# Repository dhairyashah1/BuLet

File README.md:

# BuLET: An Ultra Low Energy Transmitter

This repository contains the code and artifacts for **BuLet** which is developed as a part of CS5272: Embedded Software Design Course Project, Spring 2025 held at NUS.

> The BuLET system aims to enable low-power BLE
advertisement transmissions in the 1M / 2M PHY modes with
the provision of Extended PHY later. These transmissions are
decodable by commodity BLE receivers like smartphones:

<div align="center">

</div>

## Abstract

Increased embedded system deployments have driven the widespread adoption of various wireless standards. Commonly used protocols include Wi-Fi, Bluetooth, ZigBee, and LoRa operate in the Industrial, Scientific and Medical bands (ISM) i.e. 868 MHz and 2.4 GHz showing their ubiquity and allowance for unlicensed transmissions. Despite advancements in low-power sensors and microcontrollers, the wireless radio subsystem—particularly its analog front end—remains a major power bottleneck in embedded IoT devices. Classic Bluetooth and Bluetooth Low Energy (BLE) dominate short-range wireless communication in the 2.4 GHz spectrum, with BLE favored for its energy efficiency in lightweight, battery-powered applications. However, even state-of-the-art BLE transmitters typically consume around 20 mW  to hundreds to milliwatts, limiting lifetime for battery-operated devices. Existing low-power solutions, such as BLE backscatter, decrease transmission power but rely on external emitters to generate carrier signals, which incurs additional energy costs. Tunnel diode oscillators present another option for generating radio signals with power consumption below 100 µW but face stability issues. In this work, we introduce BuLET, an ultra-low-power Bluetooth transmitter that integrate both backscatter and tunnel diode oscillator (TDO)-based frontends with a commercial microcontroller to generate BLE-compliant advertisements for unidirectional communication. We also demonstrate sub-harmonic injection locking to stabilize the TDO for reliable communication.

## Contributions

1.  BuLET is a compact (10cm x 5cm) system built using off-the-shelf components. It houses a low-power microcontroller for baseband generation and processing combining both **tunnel diode** based and **backscatter** frontends. This enables energy-efficient unidirectional BLE advertisments}= for sustainable communication.
2. Extending on Judo architecture, BuLET stabilizes the TDO from resonant frequency shifts by injection-locking lower-frequency sub-harmonic of TDO at **1.239 GHz** (**sub-harmonic injection locking**, min strength = 50 dBm). This supports the argument that lower-frequency signals are easier to generate from commodity devices. 
3. BuLET has a total power consumption of under **250 µW** which includes the baseband generator and frontends.
4. BuLET's transmissions are compatible to be received by commodity BLE receivers like smartphones and tablets.

## Repository Organization

```
├── LICENSE
├── README.md
├── assets                     # pictures, plots and images
│   ├── backscatter_frontend
│   ├── baseband_generator
│   └── tdo_frontend
├── data_logs                  # spectrum analyzer data
│   ├── cabled_spectrum
│   └── wireless_spectrum
├── examples
├── firmware                   # firmware implementations for BLE baseband
│   ├── beaglebone             # (1) beaglebone black implementation using PRU
│   └── ble_baseband_5969      # (2) msp430 implementation 
└── hardware                   # hardware PCB design files for BuLET designed in eagle
    ├── README.md             
    ├── backscatter_frontend
    ├── baseband_generator
    └── tdo_frontend
```

## Hardware Design

### Platform and Baseband Generator

The hardware platform prototype of the BuLET
system consists of a baseband generator and both backscatter
and tunnel diode based frontends to support low-power BLE
transmissions.

<div align="center">

</div>

### Tunnel Diode Oscillator Frontend

A tunnel diode oscillator built using a 1N3712 tunnel diode and passive RLC components. It oscillates at the following frequencies measured in a cabled setup.
- Principal frequency = 1.23 GHz, -26 dBm
- Second harmonic frequency = 2.47 GHz, -45 dBm

<div align="center">

</div>

Spectrum of unmodulated carrier signals generated by TDO captured in a cabled setup.

<div align="center">

</div>

Spectrum of the modulated / mixed signal after sub-harmonic injection locking captured in a wireless setup. The carrier signals generated by TDO, after mixing with the BLE baseband signal represents the mixed signal. The lower-order or principal harmonic at 1.23 GHz is injection locked, which also stabilizes the second harmonic at 2.47 GHz. Minimum injection locking strength is reported to be as -50 dBm.

<div align="center">

</div>

# Evaluation

### Evaluation Setup
<div align="center">

</div>

### Backscatter Frontend

Signal strength of the BLE advertisements (mixed signal) recorded on a spectrum analyzer at various distances in a LoS setting with changing distances between the carrier emitter and the tag: 0.5 m, 1 m, 1.5 m, 2 m.

<div align="center">

</div>

### Performance Comparison of Frontends

TDO frontend achieves a minimal range of 1 m as compared to 5.5 m by backscatter when the carrier emitter / injection locking device are kept each 1.5 m away from the tag. This is due to the weak carrier signal generated by TDO and even weaker mixed signal at 2.478 GHz (39th Advertisement channel).

<div align="center">

</div>

### Reception

Successful reception of BuLET generated BLE advertisements from either frontends on a capable commodity smartphone.

<div align="center">

</div>

### Power consumption 

Comparison of power consumption and lifetime of BuLET with different wireless technologies on a 225 mAh CR2032 battery.

| **Technology**                  | **Power Consumption** | **Lifetime (225 mAh battery)** |
|:---------------------------------|:----------------------:|:------------------------------:|
| **Active Classic Bluetooth TX**  | 0.5 - 1 W              | 40 minutes                    |
| **Active BLE TX**                | 20 - 100 mW            | 15 hours                      |
| **BuLET Backscatter TX**         | 150 μW                  | 80 - 100 days                |
| **BuLET Tunnel diode TX**        | 250 μW                  | 50 - 80 days                 |

## Limitations

- Early prototype of a low-power BLE transmitter using tunnel diode oscillators (TDO) and sub-harmonic injection locking.
- Current TDO is unable to:
  - Generate stronger signal strength at the second harmonic. OR
  - Build a TDO operating with principal harmonic at 2.478 GHz.
- These limitations affect system performance and the ability to use weaker injection locking signals.
- Achieving this would establish significant novelty over existing backscatter systems.

## Future Work
- Build a 2.4 GHz TDO with a strong principal harmonic.
- Enable various BLE modes, including:
  - LE Coded PHY (Long Range Mode).
  - Frequency hopping on simple systems like BuLET.

## Acknowledgements

This project is completed and submitted to fulfill the requirements of CS5272: Embedded Software Design course at NUS (Spring 2025). I acknowledge and thank Prof. Ambuj Varshney for his support and guidance throughout this course.

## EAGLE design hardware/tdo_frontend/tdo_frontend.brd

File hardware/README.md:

# Hardware Design Files

PCB Design Files for BuLET Platform - TDO | Backscatter Tag | MSP430 - Baseband Generator

These are designed using Eagle software. Please install it on your relevant Operating System.

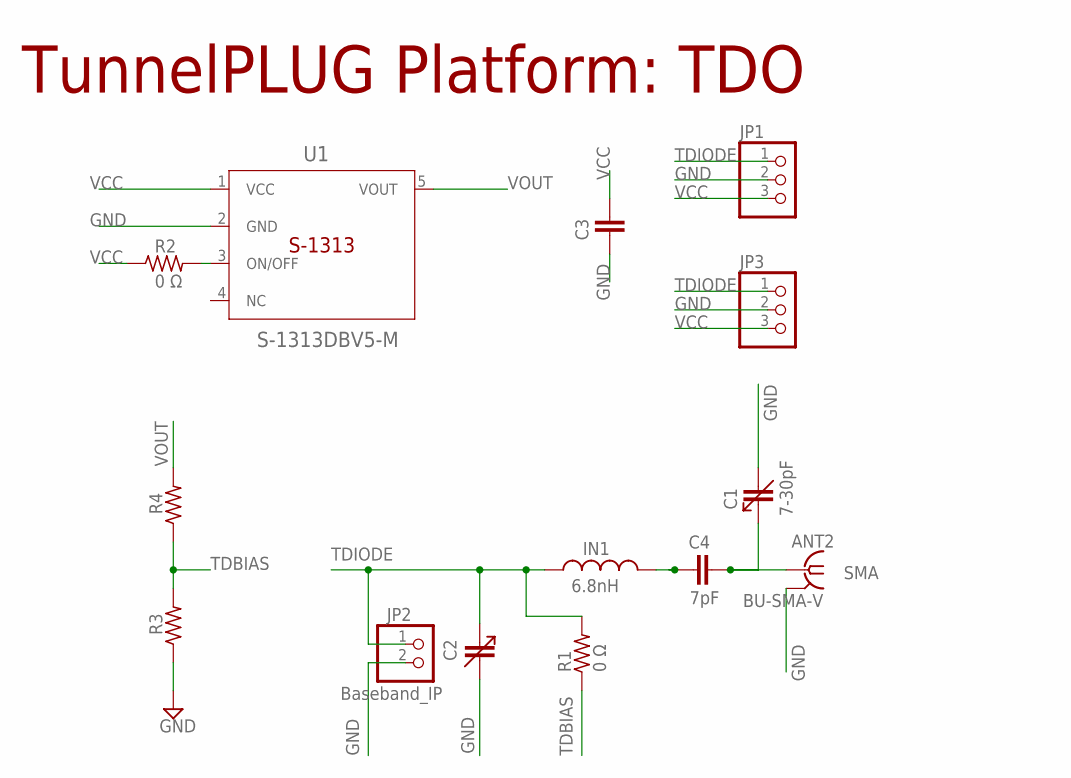
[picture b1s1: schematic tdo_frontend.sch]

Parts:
C1, C2: 7-30pF; CTZ3
C3: CAPACITOR; C0603
C4: 7pF; C0603
IN1: 6.8nH; 0603_1PRIMARY
JP1: PINHD-1X3/90; 1X03/90
JP2: Baseband_IP; 1X02
JP3: PINHD-1X3/LONG; 1X03
R1, R2: 0 Ω; R0603
R3, R4: R-US_R0603; R0603
SMA: BU-SMA-V
U1: S-1313DBV5-M; DBV5-M

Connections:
ANT2: C1.+ (3), C4.2, SMA.1
GND: C1.- (4), C2.- (4), C3.1, JP1.2, JP2.2, JP3.2, R3.1, SMA.2, SMA.3 (2), SMA.4 (2), SMA.5 (2), U1.2 (GND)
unnamed: R2.2, U1.3 (ON/OFF)
unnamed: C4.1, IN1.2
TDBIAS: R1.1, R3.2, R4.1
TDIODE: C2.+ (3), IN1.1, JP1.1, JP2.1, JP3.1, R1.2
VCC: C3.2, JP1.3, JP3.3, R2.1, U1.1 (VCC)
VOUT: R4.2, U1.5 (VOUT)

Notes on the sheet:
TunnelPLUG Platform: TDO

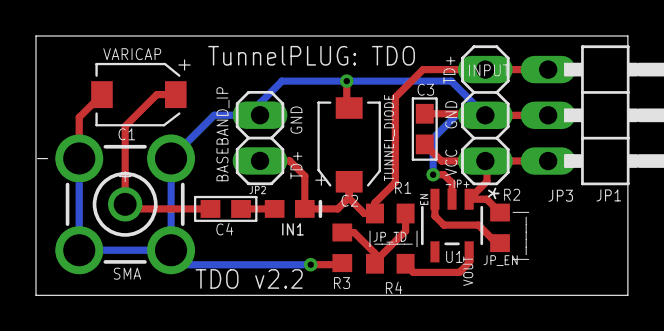
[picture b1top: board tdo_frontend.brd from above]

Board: 2 copper layers, 32.9 x 14.4 mm, 14 parts (0 on the bottom side), 8 nets.

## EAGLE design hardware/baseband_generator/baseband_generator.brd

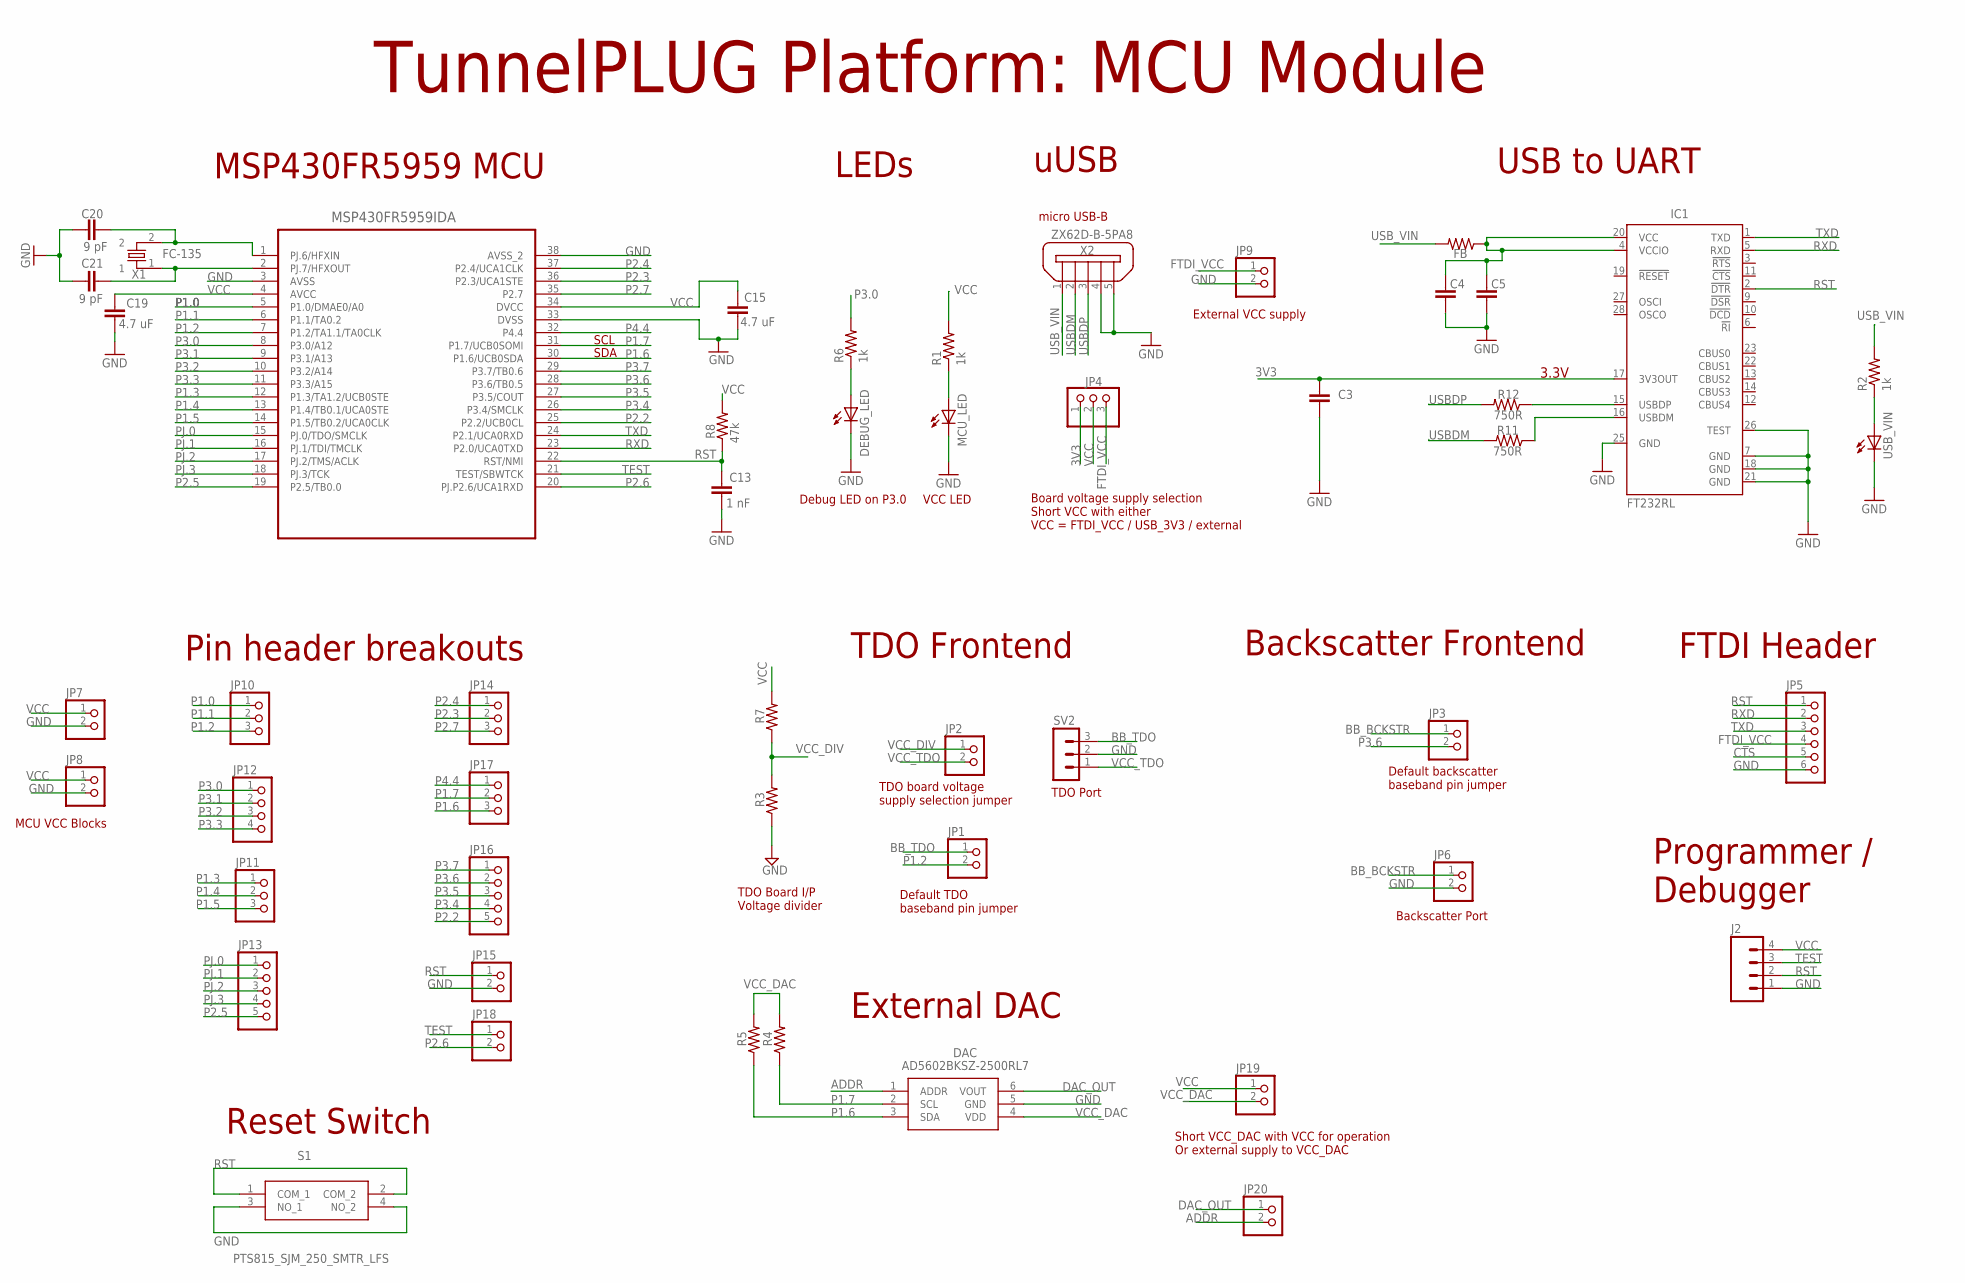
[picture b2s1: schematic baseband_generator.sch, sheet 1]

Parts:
C3, C4, C5: 0805_1; 0805_1PRIMARY
C13: 1 nF; C0603
C15, C19: 4.7 uF; C0603
C20, C21: 9 pF; C0603
DAC: AD5602BKSZ-2500RL7; SOT65P210X110-6N
DEBUG_LED: LED0603; LED-0603
FB: RESISTOR0805-RES; 0805
IC1: FT232RL; SSOP28
J2: MHDR1X4_1; MHDR1X4_1PRIMARY
JP1, JP2, JP3: PINHD-1X2/LOCK; 1X02/LOCK
JP4: PINHD-1X3/LOCK; 1X03/LOCK
JP5: PINHD-1X6/90; 1X06/90
JP6, JP7, JP8, JP9, JP15, JP18, JP19, JP20: PINHD-1X2; 1X02
JP10, JP11, JP14, JP17: PINHD-1X3; 1X03
JP12: PINHD-1X4; 1X04
JP13, JP16: PINHD-1X5; 1X05
MCU_LED: LED0603; LED-0603
R1, R2, R6: 1k; 0805
R3, R4, R5, R7: R-US_R0603; R0603
R8: 47k; 0805
R11, R12: 750R; 0805
S1: PTS815_SJM_250_SMTR_LFS; PTS815SJM250SMTRLFS
SV2: MA03-1
U2: MSP430FR5739IDAMSP430FR5959IDA; SOP65P810X120-38N
USB_VIN: LED0603; LED-0603
X1: FC-135; FC-135_1PRIMARY
X2: ZX62D-B-5PA8

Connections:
3V3: C3.1, IC1.17 (3V3OUT), JP4.1
ADDR: DAC.1 (ADDR), JP20.2
BB_BCKSTR: JP3.1, JP6.1
BB_TDO: JP1.1, SV2.3
CTS: JP5.5
DAC_OUT: DAC.6 (VOUT), JP20.1
FTDI_VCC: JP4.3, JP5.4, JP9.1
GND: C3.2, C4.2, C5.2, C13.2, C15.1, C19.2, C20.2, C21.2, DAC.5 (GND), DEBUG_LED.C, IC1.7 (GND), IC1.18 (GND), IC1.21 (GND), IC1.25 (GND), IC1.26 (TEST), J2.1, JP5.6, JP6.2, JP7.2, JP8.2, JP9.2, JP15.2, MCU_LED.C, R3.1, S1.3 (NO_1), S1.4 (NO_2), SV2.2, U2.3 (AVSS), U2.33 (DVSS), U2.38 (AVSS_2), USB_VIN.C, X2.4, X2.5
unnamed: C21.1, U2.2 (PJ.7/HFXOUT), X1.1
unnamed: C20.1, U2.1 (PJ.6/HFXIN), X1.2
unnamed: DEBUG_LED.A, R6.1
unnamed: MCU_LED.A, R1.1
unnamed: R2.1, USB_VIN.A
unnamed: C4.1, C5.1, FB.1, IC1.4 (VCCIO), IC1.20 (VCC)
unnamed: IC1.15 (USBDP), R12.1
unnamed: IC1.16 (USBDM), R11.1
P1.0: JP10.1, U2.5 (P1.0/DMAE0/A0)
P1.1: JP10.2, U2.6 (P1.1/TA0.2)
P1.2: JP1.2, JP10.3, U2.7 (P1.2/TA1.1/TA0CLK)
P1.3: JP11.1, U2.12 (P1.3/TA1.2/UCB0STE)
P1.4: JP11.2, U2.13 (P1.4/TB0.1/UCA0STE)
P1.5: JP11.3, U2.14 (P1.5/TB0.2/UCA0CLK)
P1.6: DAC.3 (SDA), JP17.3, R5.1, U2.30 (P1.6/UCB0SDA)
P1.7: DAC.2 (SCL), JP17.2, R4.1, U2.31 (P1.7/UCB0SOMI)
P2.2: JP16.5, U2.25 (P2.2/UCB0CL)
P2.3: JP14.2, U2.36 (P2.3/UCA1STE)
P2.4: JP14.1, U2.37 (P2.4/UCA1CLK)
P2.5: JP13.5, U2.19 (P2.5/TB0.0)
P2.6: JP18.2, U2.20 (PJ.P2.6/UCA1RXD)
P2.7: JP14.3, U2.35 (P2.7)
P3.0: JP12.1, R6.2, U2.8 (P3.0/A12)
P3.1: JP12.2, U2.9 (P3.1/A13)
P3.2: JP12.3, U2.10 (P3.2/A14)
P3.3: JP12.4, U2.11 (P3.3/A15)
P3.4: JP16.4, U2.26 (P3.4/SMCLK)
P3.5: JP16.3, U2.27 (P3.5/COUT)
P3.6: JP3.2, JP16.2, U2.28 (P3.6/TB0.5)
P3.7: JP16.1, U2.29 (P3.7/TB0.6)
P4.4: JP17.1, U2.32 (P4.4)
PJ.0: JP13.1, U2.15 (PJ.0/TDO/SMCLK)
PJ.1: JP13.2, U2.16 (PJ.1/TDI/TMCLK)
PJ.2: JP13.3, U2.17 (PJ.2/TMS/ACLK)
PJ.3: JP13.4, U2.18 (PJ.3/TCK)
RST: C13.1, IC1.2 (!DTR), J2.2, JP5.1, JP15.1, R8.1, S1.1 (COM_1), S1.2 (COM_2), U2.22 (RST/NMI)
RXD: IC1.5 (RXD), JP5.2, U2.23 (P2.0/UCA0TXD)
TEST: J2.3, JP18.1, U2.21 (TEST/SBWTCK)
TXD: IC1.1 (TXD), JP5.3, U2.24 (P2.1/UCA0RXD)
USBDM: R11.2, X2.2
USBDP: R12.2, X2.3
USB_VIN: FB.2, R2.2, X2.1
VCC: C15.2, C19.1, J2.4, JP4.2, JP7.1, JP8.1, JP19.1, R1.2, R7.2, R8.2, U2.4 (AVCC), U2.34 (DVCC)
VCC_DAC: DAC.4 (VDD), JP19.2, R4.2, R5.2
VCC_DIV: JP2.1, R3.2, R7.1
VCC_TDO: JP2.2, SV2.1

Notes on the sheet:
MSP430FR5959 MCU
LEDs
TunnelPLUG Platform: MCU Module
uUSB
USB to UART
FTDI Header
3.3V
Board voltage supply selection Short VCC with either VCC = FTDI_VCC / USB_3V3 / external
TDO Frontend
Backscatter Frontend
Debug LED on P3.0
micro USB-B
VCC LED
Pin header breakouts
External VCC supply
Default backscatter baseband pin jumper
Default TDO baseband pin jumper
TDO board voltage supply selection jumper
TDO Port
Backscatter Port
TDO Board I/P Voltage divider
MCU VCC Blocks
Reset Switch
External DAC
Short VCC_DAC with VCC for operation Or external supply to VCC_DAC
SCL
SDA
Programmer / Debugger

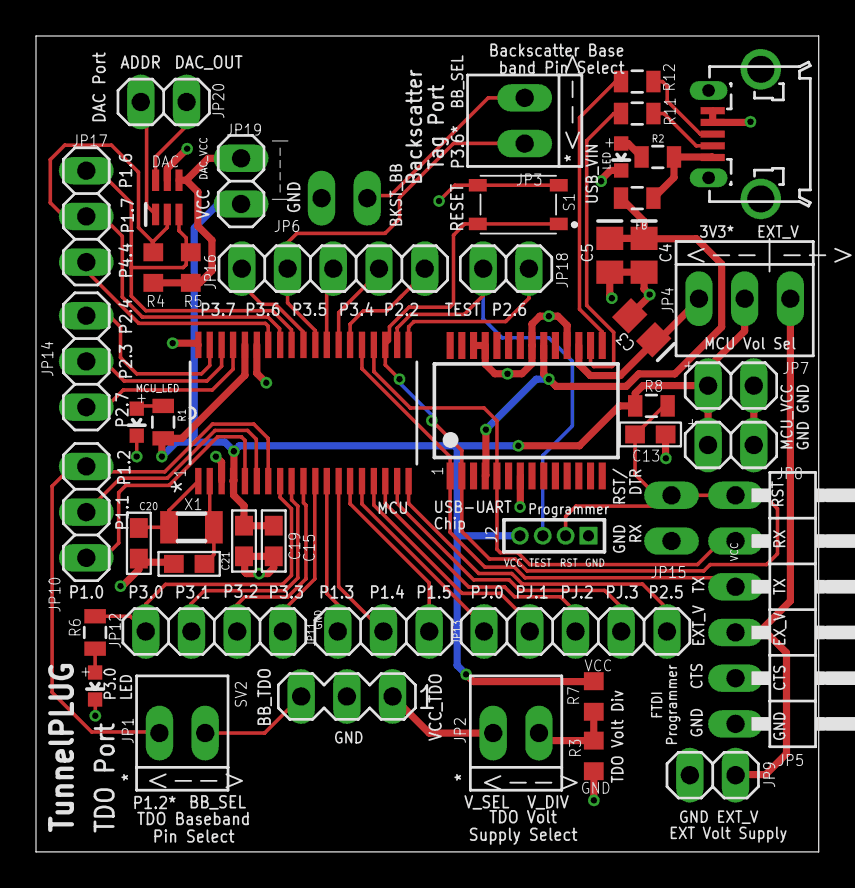
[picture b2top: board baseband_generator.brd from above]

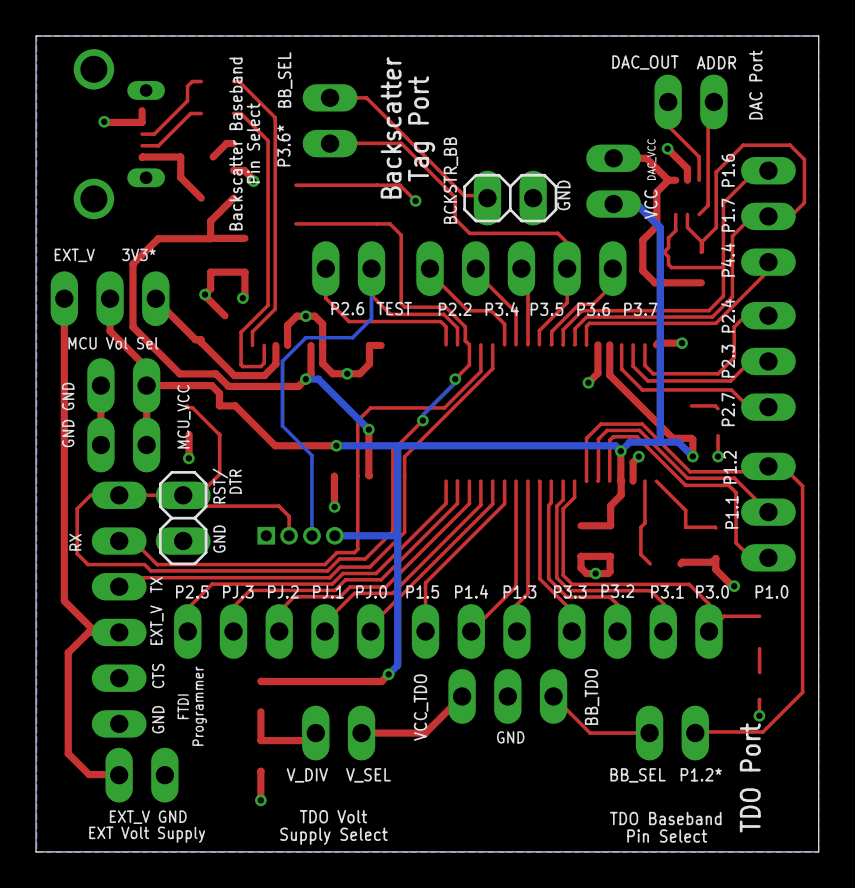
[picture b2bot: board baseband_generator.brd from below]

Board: 2 copper layers, 43.5 x 45.3 mm, 50 parts (2 on the bottom side), 53 nets.

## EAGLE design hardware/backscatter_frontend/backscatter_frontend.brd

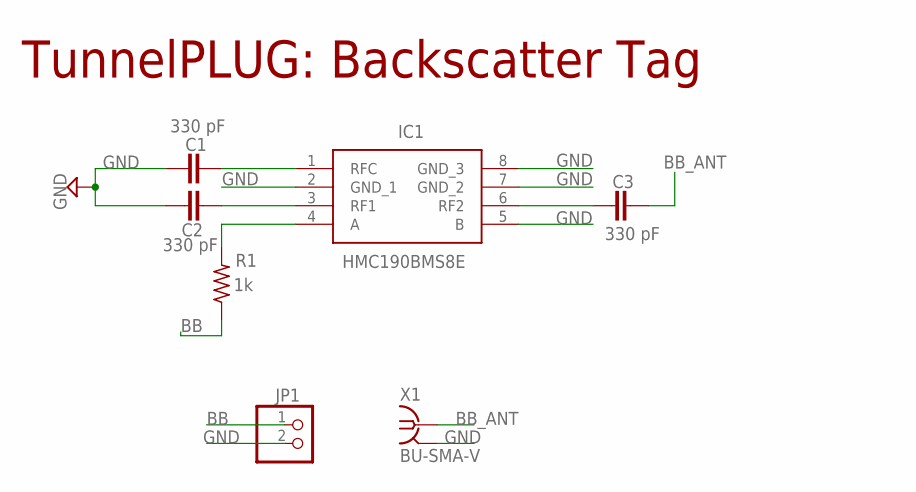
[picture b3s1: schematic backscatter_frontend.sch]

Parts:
C1, C2, C3: 330 pF; C0603K
IC1: HMC190BMS8E; SOP65P488X110-8N
JP1: PINHD-1X2/L90; 1X02/90
R1: 1k; M0805
X1: BU-SMA-V

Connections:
BB: JP1.1, R1.1
BB_ANT: C3.2, X1.1
GND: C1.1, C2.1, IC1.2 (GND_1), IC1.5 (B), IC1.7 (GND_2), IC1.8 (GND_3), JP1.2, X1.2, X1.3 (2), X1.4 (2), X1.5 (2)
unnamed: C1.2, IC1.1 (RFC)
unnamed: C2.2, IC1.3 (RF1)
unnamed: IC1.4 (A), R1.2
unnamed: C3.1, IC1.6 (RF2)

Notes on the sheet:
TunnelPLUG: Backscatter Tag

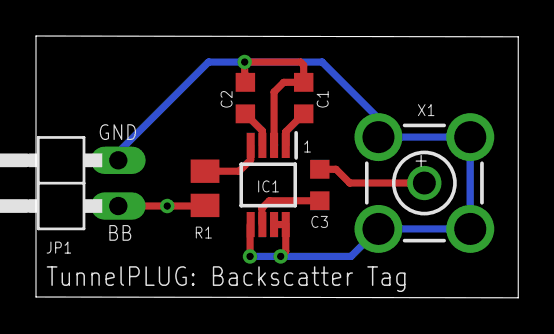
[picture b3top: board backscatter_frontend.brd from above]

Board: 2 copper layers, 26.8 x 14.5 mm, 7 parts (0 on the bottom side), 7 nets.

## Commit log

2025-04-25 Added files
2025-04-25 Adds more files
2025-04-26 Adds documentation and other files
2025-04-26 Minor fixes in README.mds

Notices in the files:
parts and their libraries:
SparkFun-Resistors: Licensing: CC v3.0 Share-Alike You are welcome to use this library for commercial purposes.
